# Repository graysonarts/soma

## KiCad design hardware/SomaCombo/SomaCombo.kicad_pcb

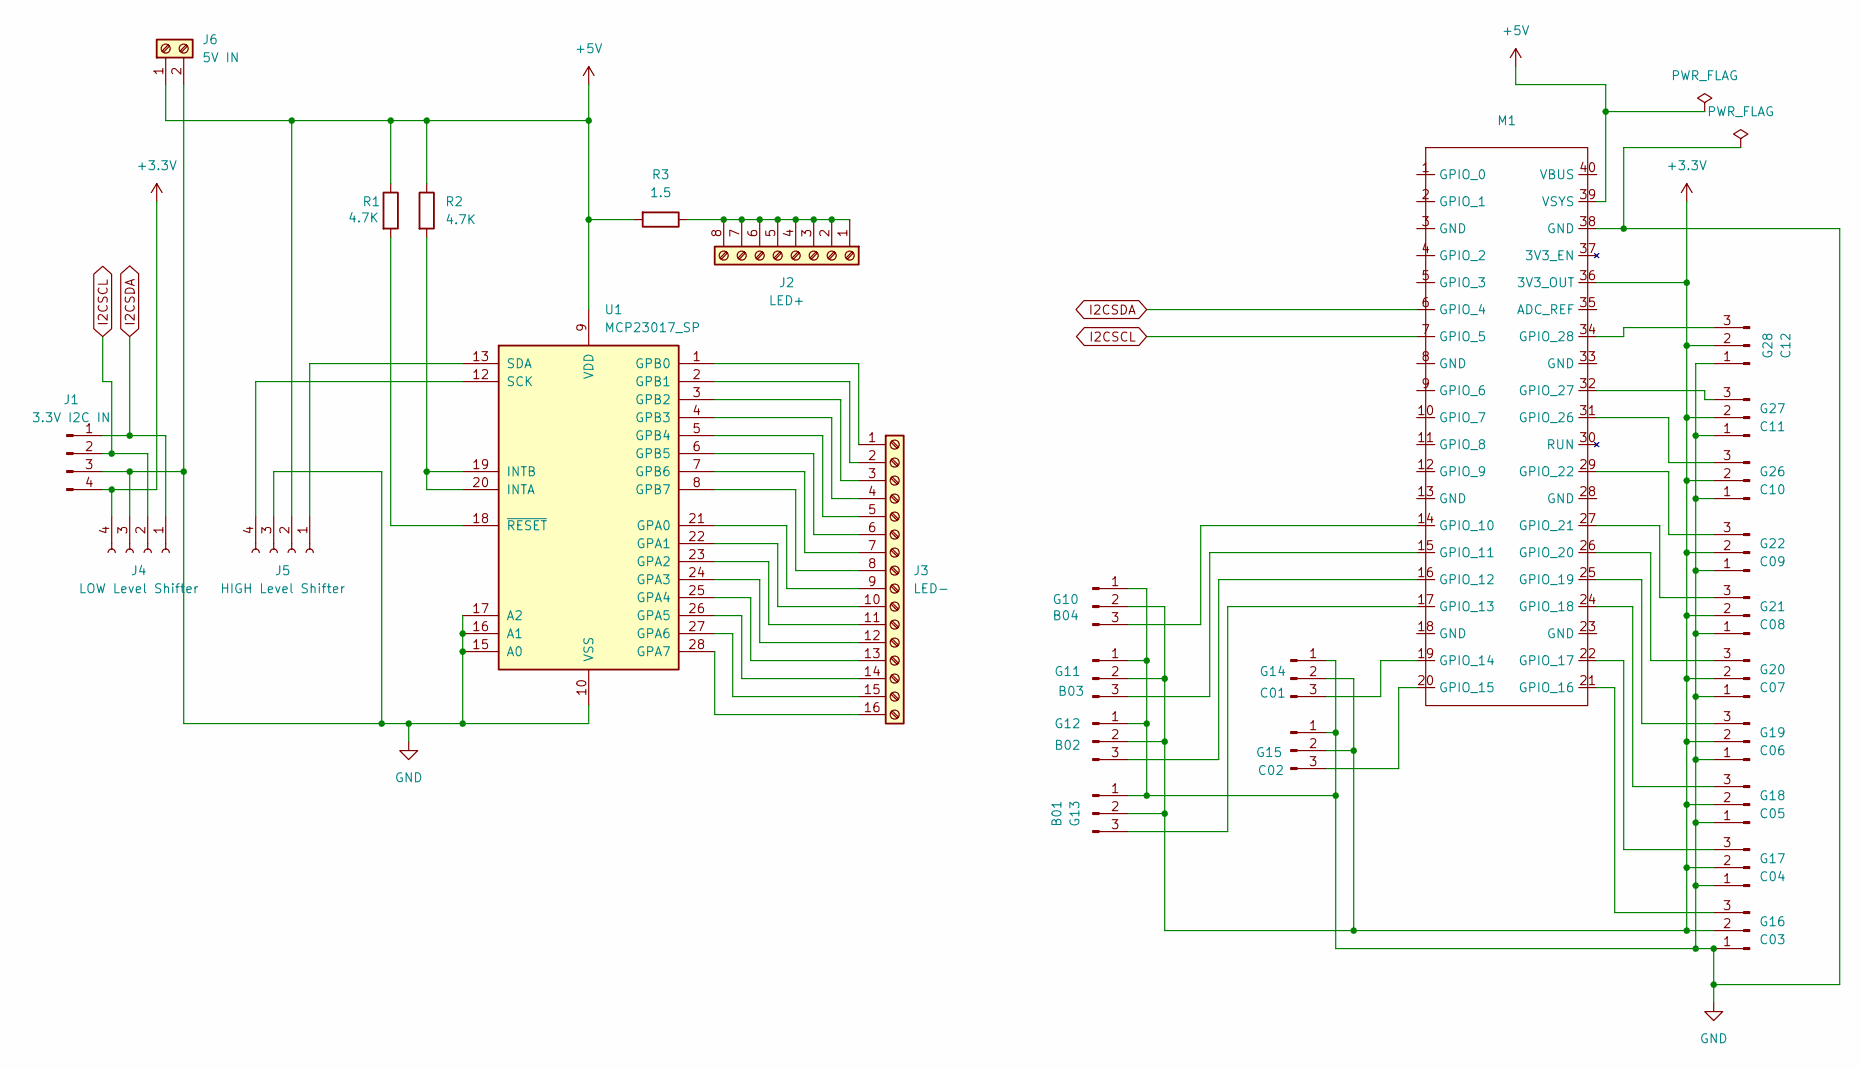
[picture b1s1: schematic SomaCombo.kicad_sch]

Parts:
G10: B04; PinHeader_1x03_P1.27mm_Vertical
G11: B03; PinHeader_1x03_P1.27mm_Vertical
G12: B02; PinHeader_1x03_P1.27mm_Vertical
G13: B01; PinHeader_1x03_P1.27mm_Vertical
G14: C01; PinHeader_1x03_P1.27mm_Vertical
G15: C02; PinHeader_1x03_P1.27mm_Vertical
G16: C03; PinHeader_1x03_P1.27mm_Vertical
G17: C04; PinHeader_1x03_P1.27mm_Vertical
G18: C05; PinHeader_1x03_P1.27mm_Vertical
G19: C06; PinHeader_1x03_P1.27mm_Vertical
G20: C07; PinHeader_1x03_P1.27mm_Vertical
G21: C08; PinHeader_1x03_P1.27mm_Vertical
G22: C09; PinHeader_1x03_P1.27mm_Vertical
G26: C10; PinHeader_1x03_P1.27mm_Vertical
G27: C11; PinHeader_1x03_P1.27mm_Vertical
G28: C12; PinHeader_1x03_P1.27mm_Vertical
J1: 3.3V I2C IN; PinHeader_1x04_P1.27mm_Vertical
J2: LED+; TerminalBlock_Phoenix_MPT-0,5-8-2.54_1x08_P2.54mm_Horizontal
J3: LED-; TerminalBlock_Xinya_XY308-2.54-16P_1x16_P2.54mm_Horizontal
J4: LOW Level Shifter; PinHeader_1x04_P1.27mm_Vertical
J5: HIGH Level Shifter; PinHeader_1x04_P1.27mm_Vertical
J6: 5V IN; TerminalBlock_Phoenix_MPT-0,5-2-2.54_1x02_P2.54mm_Horizontal
M1: Pico-W Socket
R1, R2: 4.7K; R_Axial_DIN0207_L6.3mm_D2.5mm_P7.62mm_Horizontal
R3: 1.5; R_Axial_DIN0207_L6.3mm_D2.5mm_P7.62mm_Horizontal
U1: MCP23017_SP; DIP-28_W7.62mm

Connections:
+3.3V: G10.2, G11.2, G12.2, G13.2, G14.2, G15.2, G16.2, G17.2, G18.2, G19.2, G20.2, G21.2, G22.2, G26.2, G27.2, G28.2, J1.4, J4.4, M1.36 (3V3_OUT)
+5V: J5.2, J6.1, M1.39 (VSYS), R1.1, R2.1, R3.2, U1.9 (VDD)
GND: G10.1, G11.1, G12.1, G13.1, G14.1, G15.1, G16.1, G17.1, G18.1, G19.1, G20.1, G21.1, G22.1, G26.1, G27.1, G28.1, J1.3, J4.3, J5.3, J6.2, M1.38 (GND), U1.10 (VSS), U1.15 (A0), U1.16 (A1), U1.17 (A2)
I2CSCL: J1.2, J4.2, M1.7 (GPIO_5)
I2CSDA: J1.1, J4.1, M1.6 (GPIO_4)
unnamed: G10.3, M1.14 (GPIO_10)
unnamed: G11.3, M1.15 (GPIO_11)
unnamed: G12.3, M1.16 (GPIO_12)
unnamed: G13.3, M1.17 (GPIO_13)
unnamed: G14.3, M1.19 (GPIO_14)
unnamed: G15.3, M1.20 (GPIO_15)
unnamed: G16.3, M1.21 (GPIO_16)
unnamed: G17.3, M1.22 (GPIO_17)
unnamed: G18.3, M1.24 (GPIO_18)
unnamed: G19.3, M1.25 (GPIO_19)
unnamed: G20.3, M1.26 (GPIO_20)
unnamed: G21.3, M1.27 (GPIO_21)
unnamed: G22.3, M1.29 (GPIO_22)
unnamed: G26.3, M1.31 (GPIO_26)
unnamed: G27.3, M1.32 (GPIO_27)
unnamed: G28.3, M1.34 (GPIO_28)
unnamed: J2.1, J2.2, J2.3, J2.4, J2.5, J2.6, J2.7, J2.8, R3.1
unnamed: J3.1, U1.1 (GPB0)
unnamed: J3.2, U1.2 (GPB1)
unnamed: J3.3, U1.3 (GPB2)
unnamed: J3.4, U1.4 (GPB3)
unnamed: J3.5, U1.5 (GPB4)
unnamed: J3.6, U1.6 (GPB5)
unnamed: J3.7, U1.7 (GPB6)
unnamed: J3.8, U1.8 (GPB7)
unnamed: J3.9, U1.21 (GPA0)
unnamed: J3.10, U1.22 (GPA1)
unnamed: J3.11, U1.23 (GPA2)
unnamed: J3.12, U1.24 (GPA3)
unnamed: J3.13, U1.25 (GPA4)
unnamed: J3.14, U1.26 (GPA5)
unnamed: J3.15, U1.27 (GPA6)
unnamed: J3.16, U1.28 (GPA7)
unnamed: J5.1, U1.13 (SDA)
unnamed: J5.4, U1.12 (SCK)
unnamed: R2.2, U1.19 (INTB), U1.20 (INTA)
unnamed: R1.2, U1.18 (~RESET)

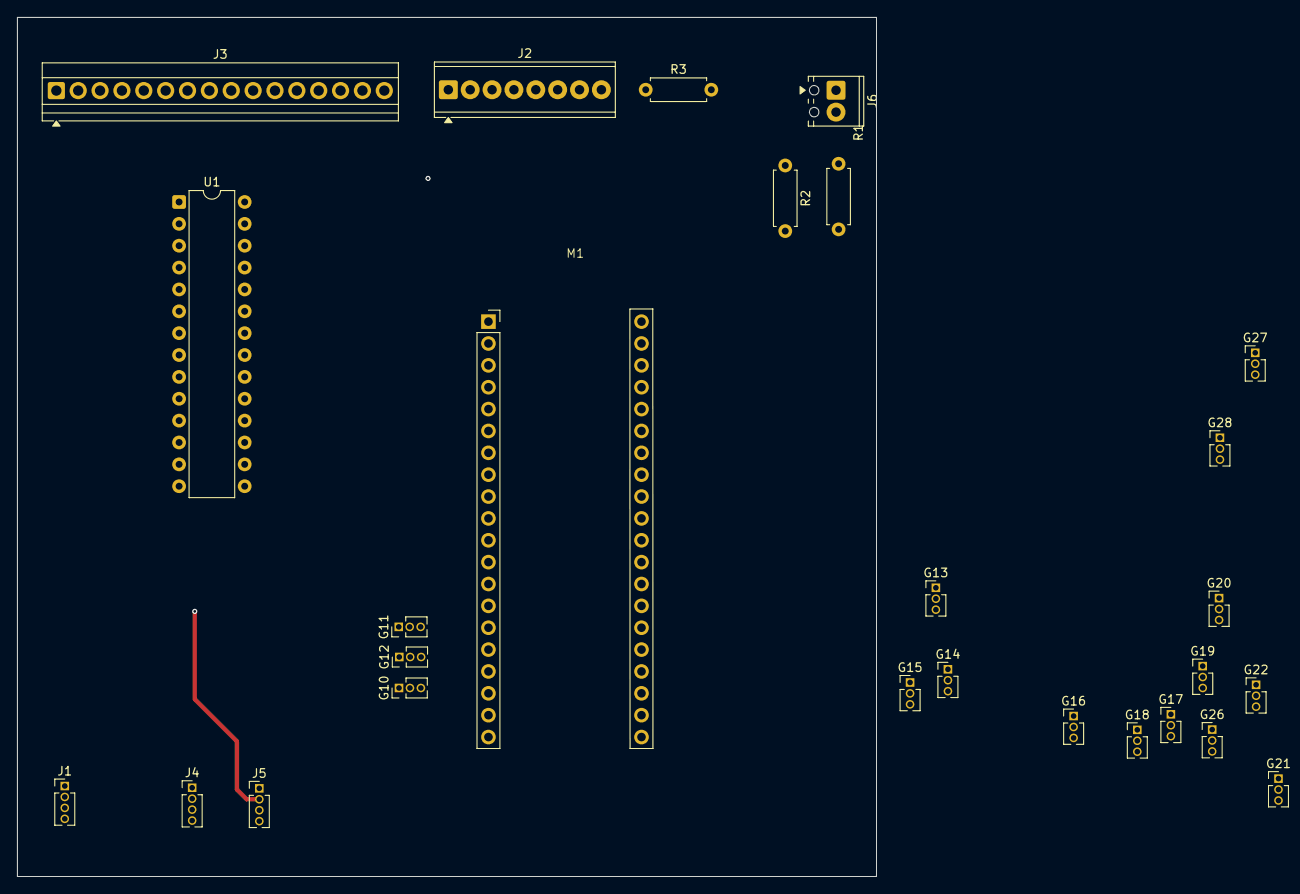
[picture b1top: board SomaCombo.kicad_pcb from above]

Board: 4 copper layers, 99.8 x 99.8 mm, 27 parts (0 on the bottom side), 42 nets.

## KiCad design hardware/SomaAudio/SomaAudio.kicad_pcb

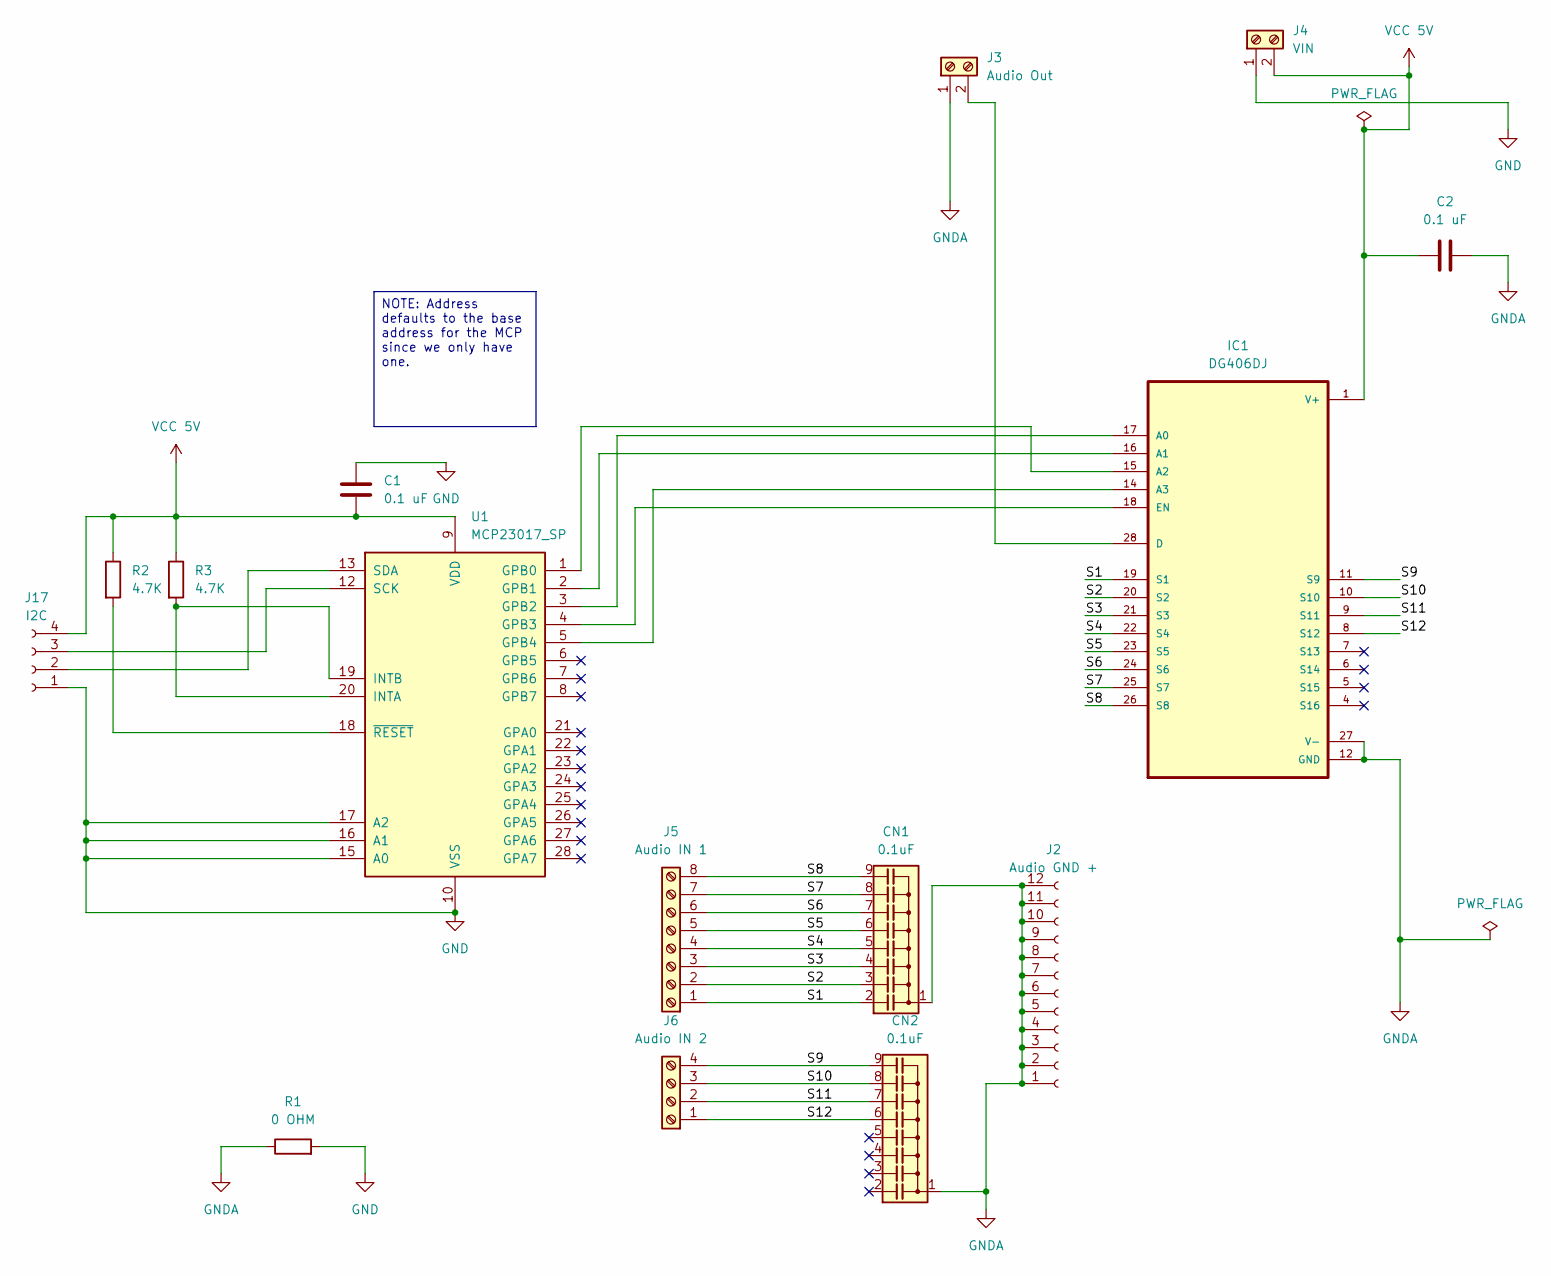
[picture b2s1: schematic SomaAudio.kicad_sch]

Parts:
C1, C2: 0.1 uF; C_Axial_L3.8mm_D2.6mm_P7.50mm_Horizontal
CN1, CN2: 0.1uF; SIP-9_21.54x3mm_P2.54mm
IC1: DG406DJ; DG407
J2: Audio GND +; TerminalBlock_Phoenix_MPT-0,5-12-2.54_1x12_P2.54mm_Horizont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
J3: Audio Out; TerminalBlock_Phoenix_MPT-0,5-2-2.54_1x02_P2.54mm_Horizontal
J4: VIN; TerminalBlock_Phoenix_MPT-0,5-2-2.54_1x02_P2.54mm_Horizontal
J5: Audio IN 1; TerminalBlock_Phoenix_MPT-0,5-8-2.54_1x08_P2.54mm_Horizontal
J6: Audio IN 2; TerminalBlock_Phoenix_MPT-0,5-4-2.54_1x04_P2.54mm_Horizontal
J17: I2C; JST_EH_S4B-EH_1x04_P2.50mm_Horizontal
R1: 0 OHM; R_Axial_DIN0204_L3.6mm_D1.6mm_P5.08mm_Horizontal
R2, R3: 4.7K; R_Axial_DIN0204_L3.6mm_D1.6mm_P5.08mm_Horizontal
U1: MCP23017_SP; DIP-28_W7.62mm

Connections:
/S1: CN1.2 (C1), IC1.19 (S1), J5.1
/S2: CN1.3 (C2), IC1.20 (S2), J5.2
/S3: CN1.4 (C3), IC1.21 (S3), J5.3
/S4: CN1.5 (C4), IC1.22 (S4), J5.4
/S5: CN1.6 (C5), IC1.23 (S5), J5.5
/S6: CN1.7 (C6), IC1.24 (S6), J5.6
/S7: CN1.8 (C7), IC1.25 (S7), J5.7
/S8: CN1.9 (C8), IC1.26 (S8), J5.8
/S9: CN2.9 (C8), IC1.11 (S9), J6.4
/S10: CN2.8 (C7), IC1.10 (S10), J6.3
/S11: CN2.7 (C6), IC1.9 (S11), J6.2
/S12: CN2.6 (C5), IC1.8 (S12), J6.1
GND: C1.1, J4.1, J17.1, R1.2, U1.10 (VSS), U1.15 (A0), U1.16 (A1), U1.17 (A2)
GNDA: C2.2, CN1.1 (common), CN2.1 (common), IC1.12 (GND), IC1.27 (V-), J2.1, J2.2, J2.3, J2.4, J2.5, J2.6, J2.7, J2.8, J2.9, J2.10, J2.11, J2.12, J3.1, R1.1
unnamed: IC1.17 (A0), U1.3 (GPB2)
unnamed: IC1.16 (A1), U1.2 (GPB1)
unnamed: IC1.15 (A2), U1.1 (GPB0)
unnamed: IC1.14 (A3), U1.5 (GPB4)
unnamed: IC1.28 (D), J3.2
unnamed: IC1.18 (EN), U1.4 (GPB3)
unnamed: J17.2, U1.13 (SDA)
unnamed: J17.3, U1.12 (SCK)
unnamed: R3.2, U1.19 (INTB), U1.20 (INTA)
unnamed: R2.2, U1.18 (~RESET)
VCC 5V: C1.2, C2.1, IC1.1 (V+), J4.2, J17.4, R2.1, R3.1, U1.9 (VDD)

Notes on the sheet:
NOTE: Address defaults to the base address for the MCP since we only have one.

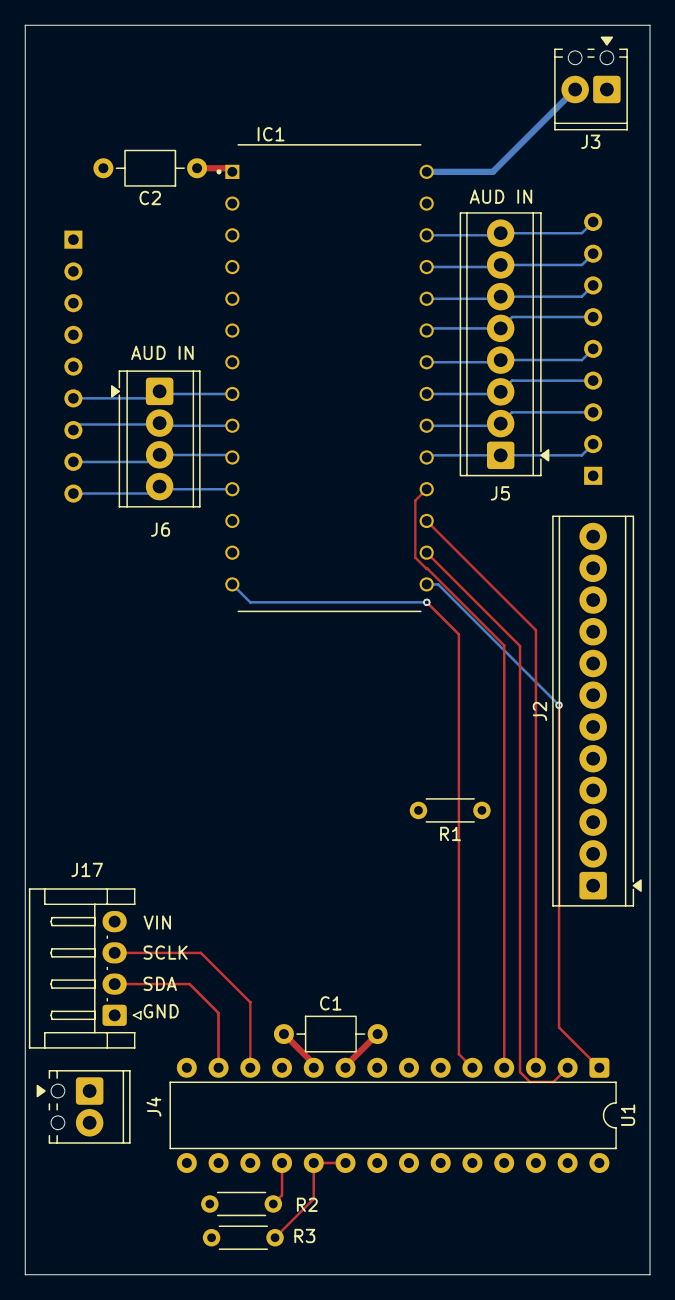
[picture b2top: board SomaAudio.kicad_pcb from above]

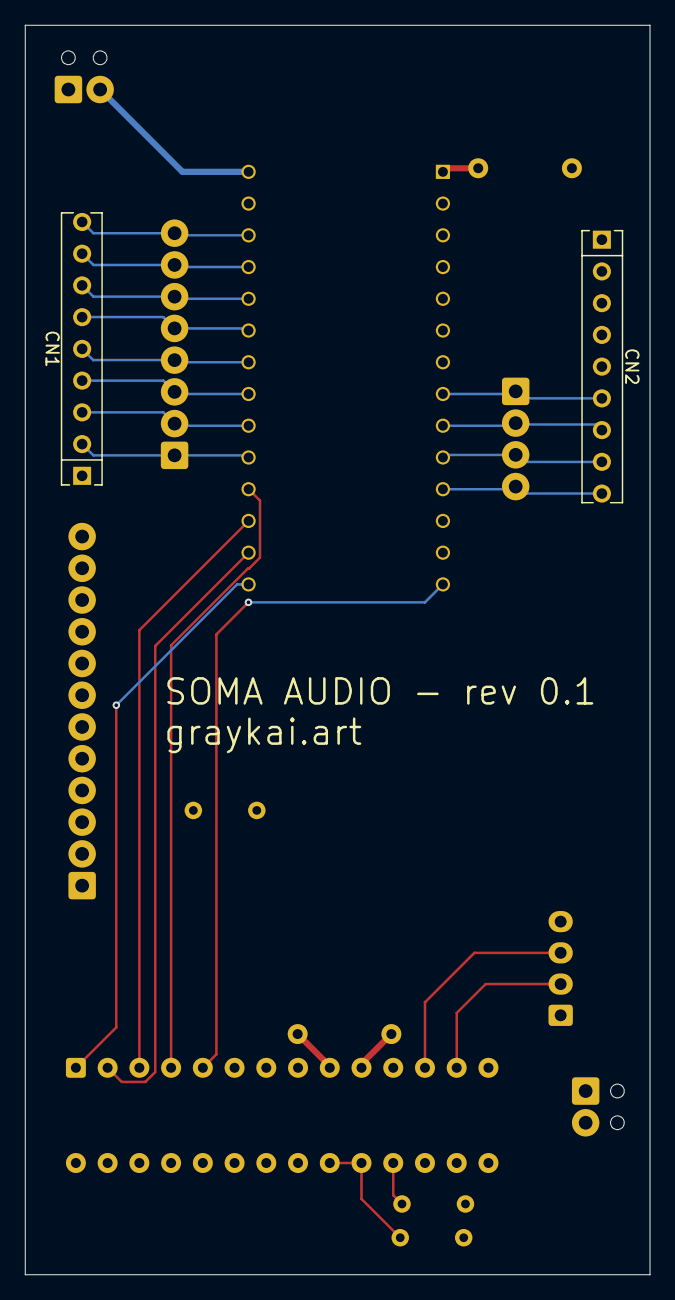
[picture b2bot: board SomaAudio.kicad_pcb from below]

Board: 4 copper layers, 50.0 x 100.0 mm, 15 parts (2 on the bottom side), 25 nets.

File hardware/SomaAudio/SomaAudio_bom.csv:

"Refs","Value","Footprint","Qty","DNP"
"C1","0.1 uF","Capacitor_THT:C_Axial_L3.8mm_D2.6mm_P7.50mm_Horizontal","1",""
"C2","0.1 uF","Capacitor_THT:C_Axial_L3.8mm_D2.6mm_P7.50mm_Horizontal","1",""
"CN1","0.1uF","Package_SIP:SIP-9_21.54x3mm_P2.54mm","1",""
"CN2","0.1uF","Package_SIP:SIP-9_21.54x3mm_P2.54mm","1",""
"IC1","DG406DJ","CustomParts:DG407","1",""
"J2","Audio GND +","TerminalBlock_Phoenix:TerminalBlock_Phoenix_MPT-0,5-12-2.54_1x12_P2.54mm_Horizontal","1",""
"J3","Audio Out","TerminalBlock_Phoenix:TerminalBlock_Phoenix_MPT-0,5-2-2.54_1x02_P2.54mm_Horizontal","1",""
"J4","VIN","TerminalBlock_Phoenix:TerminalBlock_Phoenix_MPT-0,5-2-2.54_1x02_P2.54mm_Horizontal","1",""
"J5","Audio IN 1","TerminalBlock_Phoenix:TerminalBlock_Phoenix_MPT-0,5-8-2.54_1x08_P2.54mm_Horizontal","1",""
"J6","Audio IN 2","TerminalBlock_Phoenix:TerminalBlock_Phoenix_MPT-0,5-4-2.54_1x04_P2.54mm_Horizontal","1",""
"J17","I2C","Connector_JST:JST_EH_S4B-EH_1x04_P2.50mm_Horizontal","1",""
"R1","0 OHM","Resistor_THT:R_Axial_DIN0204_L3.6mm_D1.6mm_P5.08mm_Horizontal","1",""
"R2","4.7K","Resistor_THT:R_Axial_DIN0204_L3.6mm_D1.6mm_P5.08mm_Horizontal","1",""
"R3","4.7K","Resistor_THT:R_Axial_DIN0204_L3.6mm_D1.6mm_P5.08mm_Horizontal","1",""
"U1","MCP23017_SP","Package_DIP:DIP-28_W7.62mm","1",""

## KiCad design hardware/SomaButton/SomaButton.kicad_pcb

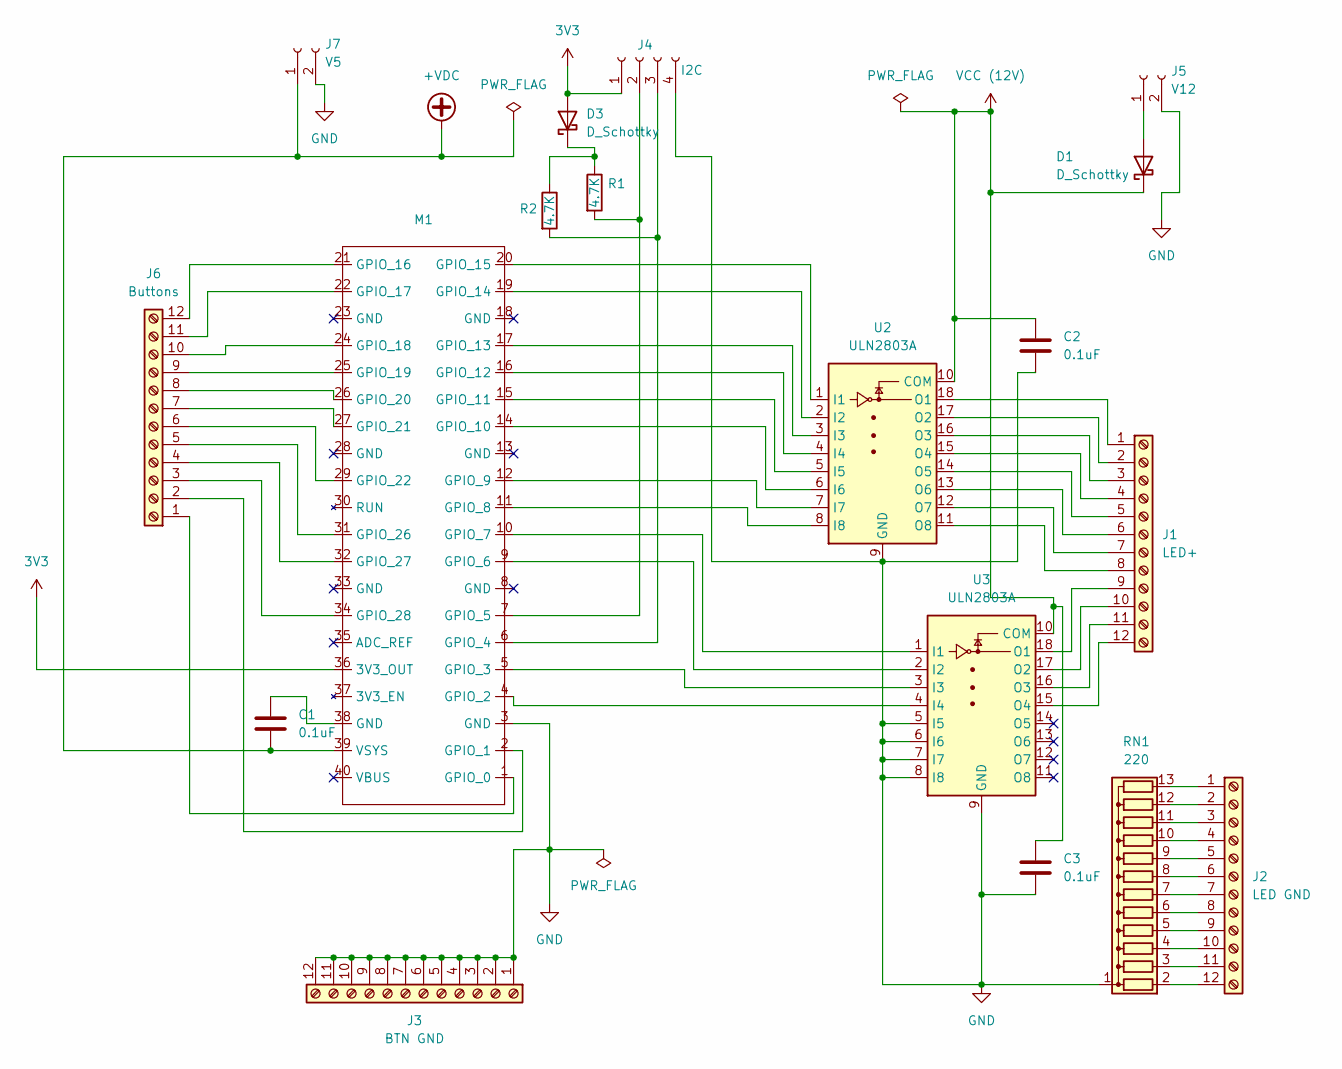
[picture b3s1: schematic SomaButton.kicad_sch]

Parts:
C1, C2, C3: 0.1uF; C_1206_3216Metric
D1, D3: D_Schottky; D_1210_3225Metric
J1: LED+; TerminalBlock_Phoenix_MPT-0,5-12-2.54_1x12_P2.54mm_Horizont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
J2: LED GND; TerminalBlock_Phoenix_MPT-0,5-12-2.54_1x12_P2.54mm_Horizont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
J3: BTN GND; TerminalBlock_Phoenix_MPT-0,5-12-2.54_1x12_P2.54mm_Horizont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
J4: I2C; JST_EH_S4B-EH_1x04_P2.50mm_Horizontal
J5: V12; TerminalBlock_Phoenix_MPT-0,5-2-2.54_1x02_P2.54mm_Horizontal
J6: Buttons; TerminalBlock_Phoenix_MPT-0,5-12-2.54_1x12_P2.54mm_Horizont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
J7: V5; TerminalBlock_Phoenix_MPT-0,5-2-2.54_1x02_P2.54mm_Horizontal
M1: Pico-W Socket
R1, R2: 4.7K; R_1210_3225Metric
RN1: 220; R_Array_SIP13
U2, U3: ULN2803A; SOIC-18W_7.5x11.6mm_P1.27mm

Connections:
3V3: D3.2 (A), J4.1, M1.36 (3V3_OUT)
+VDC: C1.2, J7.1, M1.39 (VSYS)
GND: C2.2, C3.2, J3.1, J3.2, J3.3, J3.4, J3.5, J3.6, J3.7, J3.8, J3.9, J3.10, J3.11, J3.12, J4.4, J5.2, J7.2, M1.3 (GND), RN1.1 (common), U2.9 (GND), U3.5 (I5), U3.6 (I6), U3.7 (I7), U3.8 (I8), U3.9 (GND)
unnamed: C1.1, M1.38 (GND)
unnamed: D1.2 (A), J5.1
unnamed: D3.1 (K), R1.1, R2.1
unnamed: J1.1, U2.18 (O1)
unnamed: J1.2, U2.17 (O2)
unnamed: J1.3, U2.16 (O3)
unnamed: J1.4, U2.15 (O4)
unnamed: J1.5, U2.14 (O5)
unnamed: J1.6, U2.13 (O6)
unnamed: J1.7, U2.12 (O7)
unnamed: J1.8, U2.11 (O8)
unnamed: J1.9, U3.18 (O1)
unnamed: J1.10, U3.17 (O2)
unnamed: J1.11, U3.16 (O3)
unnamed: J1.12, U3.15 (O4)
unnamed: J2.1, RN1.13 (R12)
unnamed: J2.2, RN1.12 (R11)
unnamed: J2.3, RN1.11 (R10)
unnamed: J2.4, RN1.10 (R9)
unnamed: J2.5, RN1.9 (R8)
unnamed: J2.6, RN1.8 (R7)
unnamed: J2.7, RN1.7 (R6)
unnamed: J2.8, RN1.6 (R5)
unnamed: J2.9, RN1.5 (R4)
unnamed: J2.10, RN1.4 (R3)
unnamed: J2.11, RN1.3 (R2)
unnamed: J2.12, RN1.2 (R1)
unnamed: J4.2, M1.7 (GPIO_5), R1.2
unnamed: J4.3, M1.6 (GPIO_4), R2.2
unnamed: J6.1, M1.1 (GPIO_0)
unnamed: J6.2, M1.2 (GPIO_1)
unnamed: J6.3, M1.34 (GPIO_28)
unnamed: J6.4, M1.32 (GPIO_27)
unnamed: J6.5, M1.31 (GPIO_26)
unnamed: J6.6, M1.29 (GPIO_22)
unnamed: J6.7, M1.27 (GPIO_21)
unnamed: J6.8, M1.26 (GPIO_20)
unnamed: J6.9, M1.25 (GPIO_19)
unnamed: J6.10, M1.24 (GPIO_18)
unnamed: J6.11, M1.22 (GPIO_17)
unnamed: J6.12, M1.21 (GPIO_16)
unnamed: M1.4 (GPIO_2), U3.4 (I4)
unnamed: M1.5 (GPIO_3), U3.3 (I3)
unnamed: M1.9 (GPIO_6), U3.2 (I2)
unnamed: M1.10 (GPIO_7), U3.1 (I1)
unnamed: M1.11 (GPIO_8), U2.8 (I8)
unnamed: M1.12 (GPIO_9), U2.7 (I7)
unnamed: M1.14 (GPIO_10), U2.6 (I6)
unnamed: M1.15 (GPIO_11), U2.5 (I5)
unnamed: M1.16 (GPIO_12), U2.4 (I4)
unnamed: M1.17 (GPIO_13), U2.3 (I3)
unnamed: M1.19 (GPIO_14), U2.2 (I2)
unnamed: M1.20 (GPIO_15), U2.1 (I1)
VCC (12V): C2.1, C3.1, D1.1 (K), U2.10 (COM), U3.10 (COM)

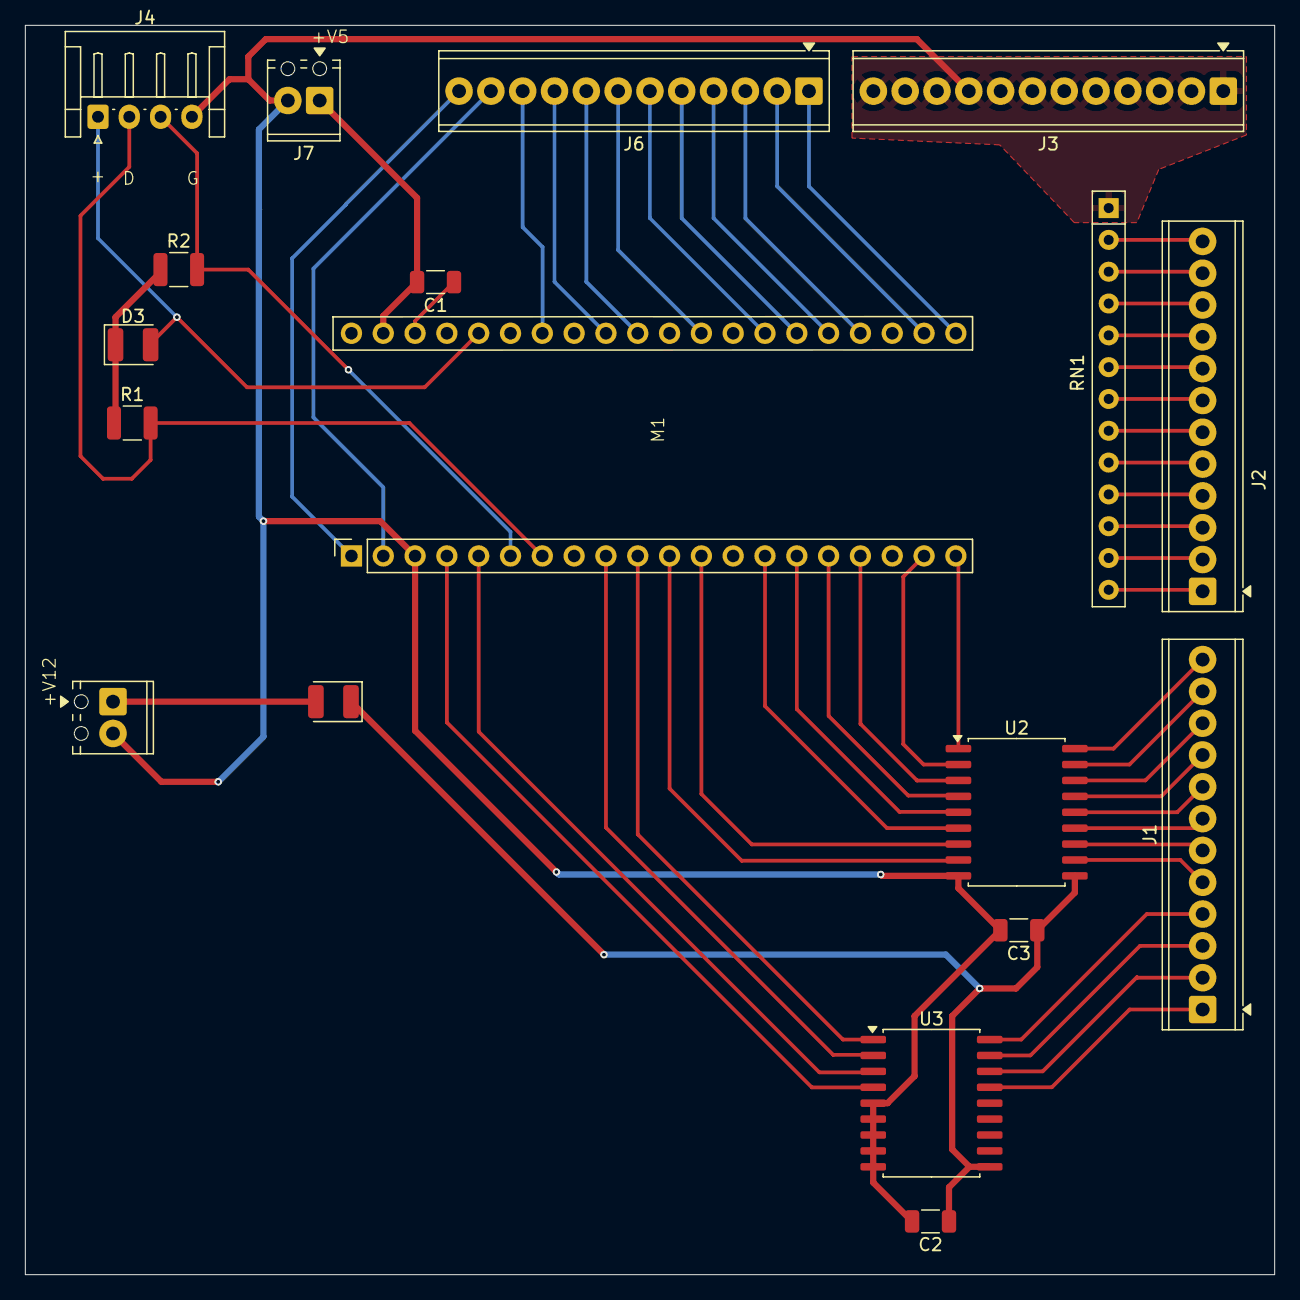
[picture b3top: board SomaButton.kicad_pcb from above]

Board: 2 copper layers, 99.8 x 99.8 mm, 18 parts (0 on the bottom side), 57 nets.

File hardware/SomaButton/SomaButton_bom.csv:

"Refs","Value","Footprint","Qty","DNP"
"C1","0.1uF","Capacitor_SMD:C_1206_3216Metric","1",""
"C2","0.1uF","Capacitor_SMD:C_1206_3216Metric","1",""
"C3","0.1uF","Capacitor_SMD:C_1206_3216Metric","1",""
"D1","D_Schottky","Diode_SMD:D_1210_3225Metric","1",""
"D3","D_Schottky","Diode_SMD:D_1210_3225Metric","1",""
"J1","LED+","TerminalBlock_Phoenix:TerminalBlock_Phoenix_MPT-0,5-12-2.54_1x12_P2.54mm_Horizontal","1",""
"J2","LED GND","TerminalBlock_Phoenix:TerminalBlock_Phoenix_MPT-0,5-12-2.54_1x12_P2.54mm_Horizontal","1",""
"J3","BTN GND","TerminalBlock_Phoenix:TerminalBlock_Phoenix_MPT-0,5-12-2.54_1x12_P2.54mm_Horizontal","1",""
"J4","I2C","Connector_JST:JST_EH_S4B-EH_1x04_P2.50mm_Horizontal","1",""
"J5","V12","TerminalBlock_Phoenix:TerminalBlock_Phoenix_MPT-0,5-2-2.54_1x02_P2.54mm_Horizontal","1",""
"J6","Buttons","TerminalBlock_Phoenix:TerminalBlock_Phoenix_MPT-0,5-12-2.54_1x12_P2.54mm_Horizontal","1",""
"J7","V5","TerminalBlock_Phoenix:TerminalBlock_Phoenix_MPT-0,5-2-2.54_1x02_P2.54mm_Horizontal","1",""
"M1","~","CustomParts:Pico-W Socket","1",""
"R1","4.7K","Resistor_SMD:R_1210_3225Metric","1",""
"R2","4.7K","Resistor_SMD:R_1210_3225Metric","1",""
"RN1","220","Resistor_THT:R_Array_SIP13","1",""
"U2","ULN2803A","Package_SO:SOIC-18W_7.5x11.6mm_P1.27mm","1",""
"U3","ULN2803A","Package_SO:SOIC-18W_7.5x11.6mm_P1.27mm","1",""

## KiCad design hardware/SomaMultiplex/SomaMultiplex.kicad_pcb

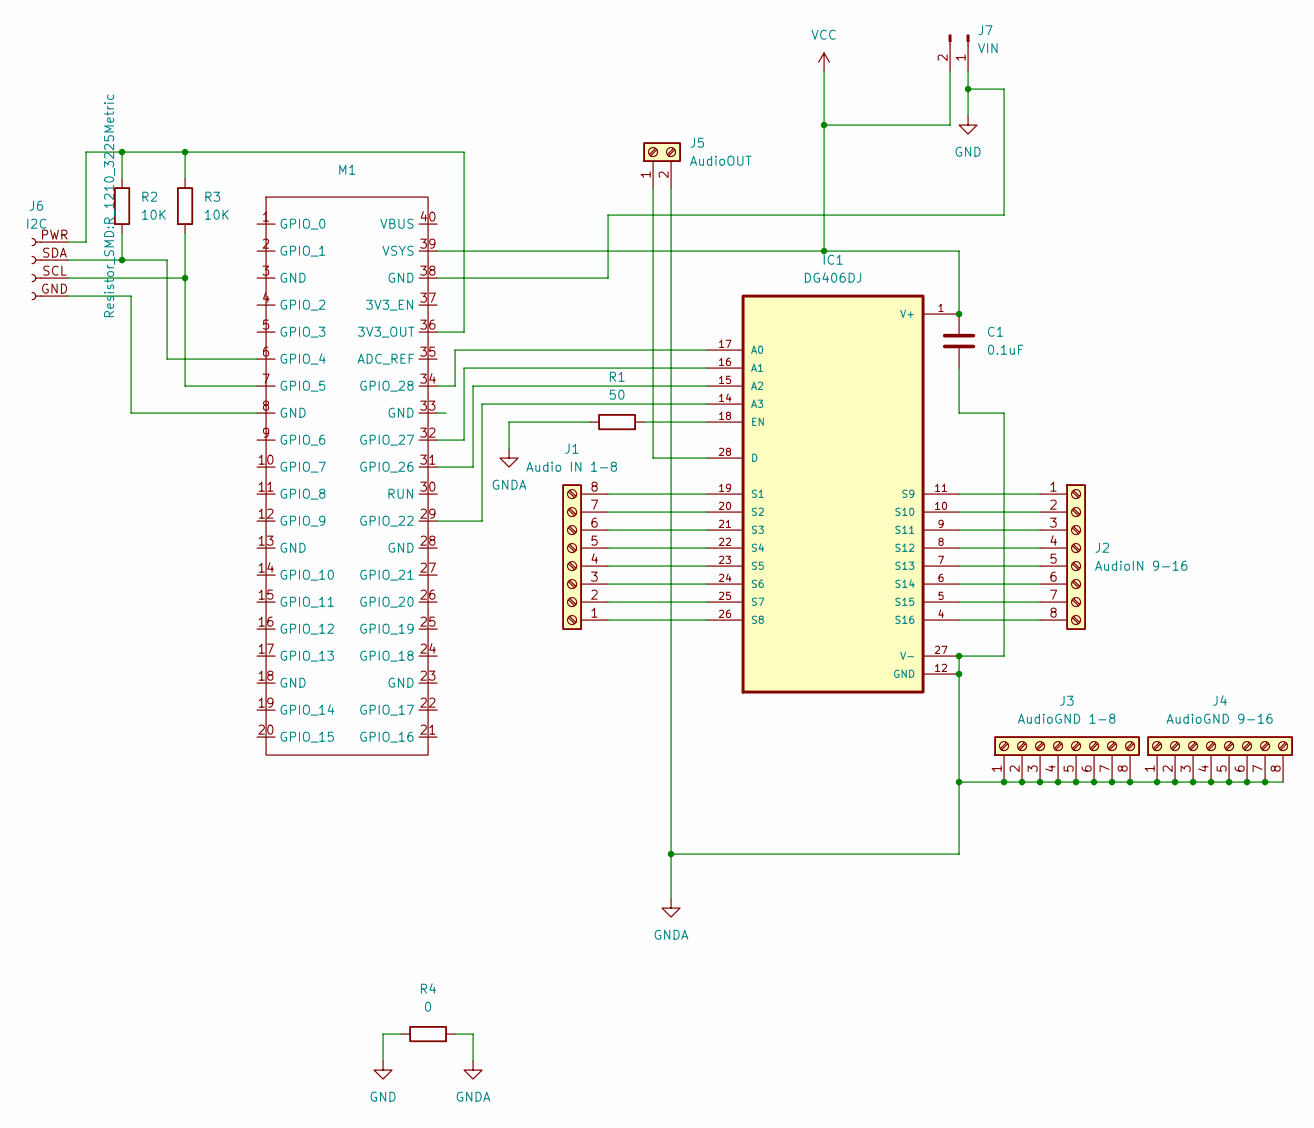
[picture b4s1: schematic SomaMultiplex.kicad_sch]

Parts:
C1: 0.1uF; C_1210_3225Metric
IC1: DG406DJ; DG407
J1: Audio IN 1-8; Altech_AK100_1x08_P5.00mm
J2: AudioIN 9-16; Altech_AK100_1x08_P5.00mm
J3: AudioGND 1-8; Altech_AK100_1x08_P5.00mm
J4: AudioGND 9-16; Altech_AK100_1x08_P5.00mm
J5: AudioOUT; Altech_AK100_1x02_P5.00mm
J6: I2C; JST_XH_S4B-XH-A-1_1x04_P2.50mm_Horizontal
J7: VIN; JST_EH_B2B-EH-A_1x02_P2.50mm_Vertical
M1: RaspberryPi_Pico_Common_THT
R1: 50; R_1210_3225Metric
R2, R3: 10K; R_1210_3225Metric
R4: 0; R_1210_3225Metric

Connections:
GND: J7.1, M1.38 (GND), R4.1
GNDA: C1.2, IC1.12 (GND), IC1.27 (V-), J3.1, J3.2, J3.3, J3.4, J3.5, J3.6, J3.7, J3.8, J4.1, J4.2, J4.3, J4.4, J4.5, J4.6, J4.7, J4.8, J5.2, R1.1, R4.2
unnamed: IC1.17 (A0), M1.34 (GPIO_28)
unnamed: IC1.16 (A1), M1.32 (GPIO_27)
unnamed: IC1.15 (A2), M1.31 (GPIO_26)
unnamed: IC1.14 (A3), M1.29 (GPIO_22)
unnamed: IC1.28 (D), J5.1
unnamed: IC1.18 (EN), R1.2
unnamed: IC1.19 (S1), J1.8
unnamed: IC1.20 (S2), J1.7
unnamed: IC1.21 (S3), J1.6
unnamed: IC1.22 (S4), J1.5
unnamed: IC1.23 (S5), J1.4
unnamed: IC1.24 (S6), J1.3
unnamed: IC1.25 (S7), J1.2
unnamed: IC1.26 (S8), J1.1
unnamed: IC1.11 (S9), J2.1
unnamed: IC1.10 (S10), J2.2
unnamed: IC1.9 (S11), J2.3
unnamed: IC1.8 (S12), J2.4
unnamed: IC1.7 (S13), J2.5
unnamed: IC1.6 (S14), J2.6
unnamed: IC1.5 (S15), J2.7
unnamed: IC1.4 (S16), J2.8
unnamed: J6.GND (Pin_1), M1.8 (GND)
unnamed: J6.SCL (Pin_2), M1.7 (GPIO_5), R3.2
unnamed: J6.SDA (Pin_3), M1.6 (GPIO_4), R2.2
unnamed: J6.PWR (Pin_4), M1.36 (3V3_OUT), R2.1, R3.1
VCC: C1.1, IC1.1 (V+), J7.2, M1.39 (VSYS)

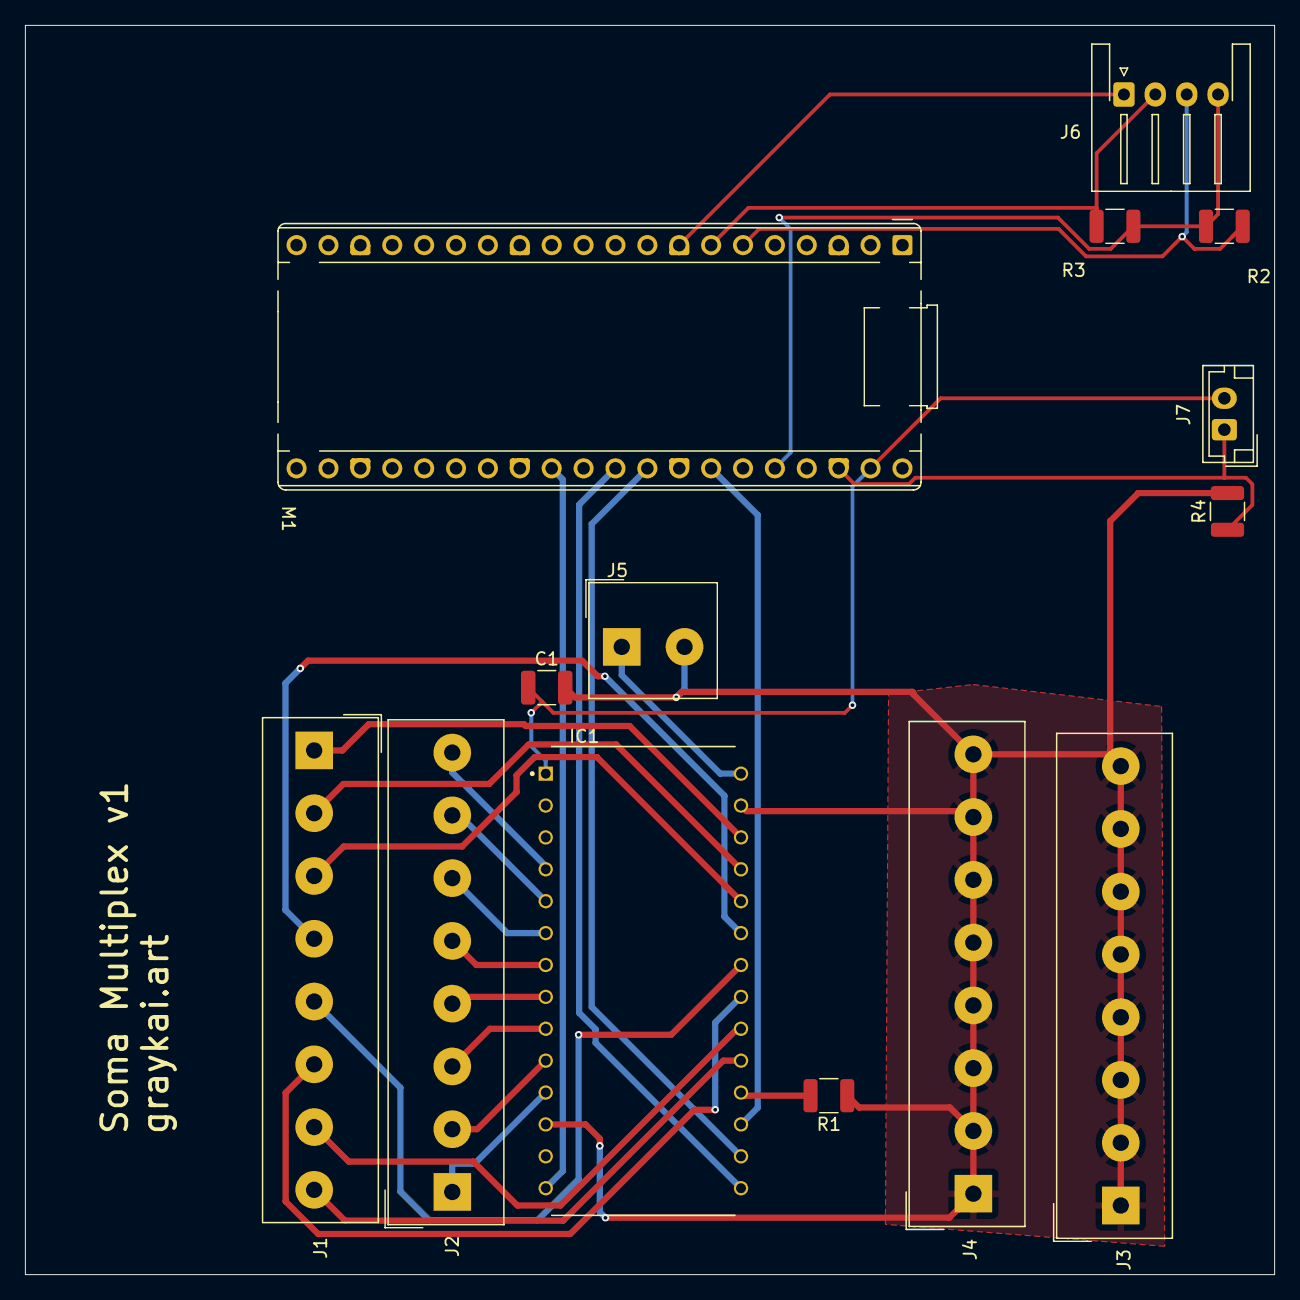
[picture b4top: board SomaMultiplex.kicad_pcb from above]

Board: 2 copper layers, 99.5 x 99.5 mm, 14 parts (0 on the bottom side), 29 nets.

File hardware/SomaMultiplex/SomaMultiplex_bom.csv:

"Refs","Value","Footprint","Qty","DNP"
"C1","0.1uF","Capacitor_SMD:C_1210_3225Metric","1",""
"IC1","DG406DJ","CustomParts:DG407","1",""
"J1","Audio IN 1-8","TerminalBlock_Altech:Altech_AK100_1x08_P5.00mm","1",""
"J2","AudioIN 9-16","TerminalBlock_Altech:Altech_AK100_1x08_P5.00mm","1",""
"J3","AudioGND 1-8","TerminalBlock_Altech:Altech_AK100_1x08_P5.00mm","1",""
"J4","AudioGND 9-16","TerminalBlock_Altech:Altech_AK100_1x08_P5.00mm","1",""
"J5","AudioOUT","TerminalBlock_Altech:Altech_AK100_1x02_P5.00mm","1",""
"J6","I2C","Connector_JST:JST_XH_S4B-XH-A-1_1x04_P2.50mm_Horizontal","1",""
"J7","VIN","Connector_JST:JST_EH_B2B-EH-A_1x02_P2.50mm_Vertical","1",""
"M1","~","Module:RaspberryPi_Pico_Common_THT","1",""
"R1","50","Resistor_SMD:R_1210_3225Metric","1",""
"R2","10K","Resistor_SMD:R_1210_3225Metric","1",""
"R3","10K","Resistor_SMD:R_1210_3225Metric","1",""
"R4","0","Resistor_SMD:R_1210_3225Metric","1",""
